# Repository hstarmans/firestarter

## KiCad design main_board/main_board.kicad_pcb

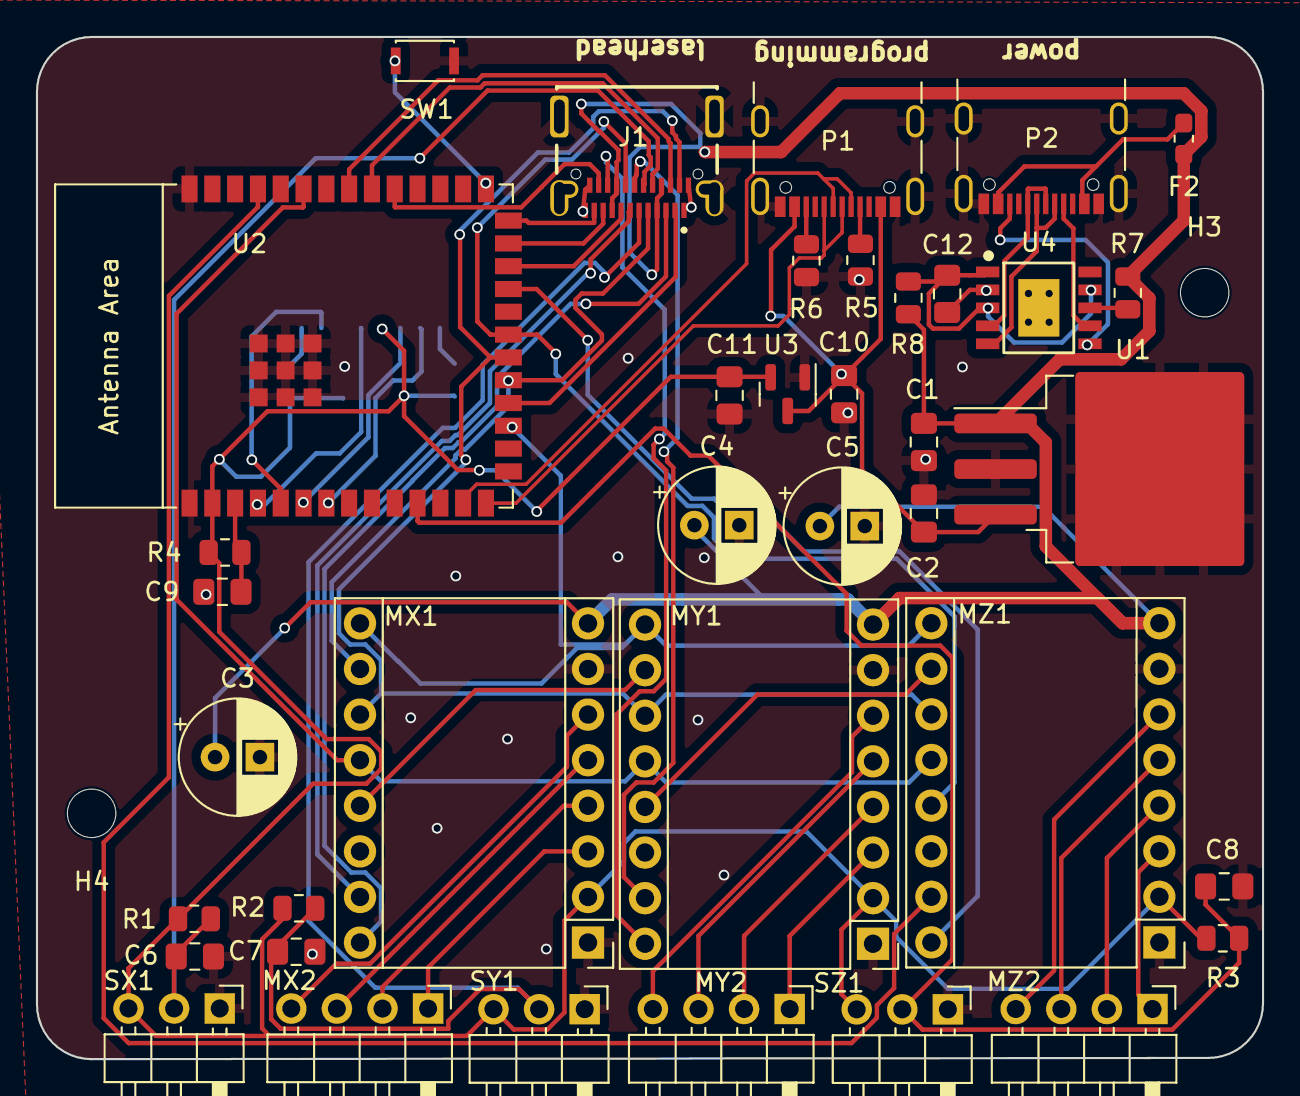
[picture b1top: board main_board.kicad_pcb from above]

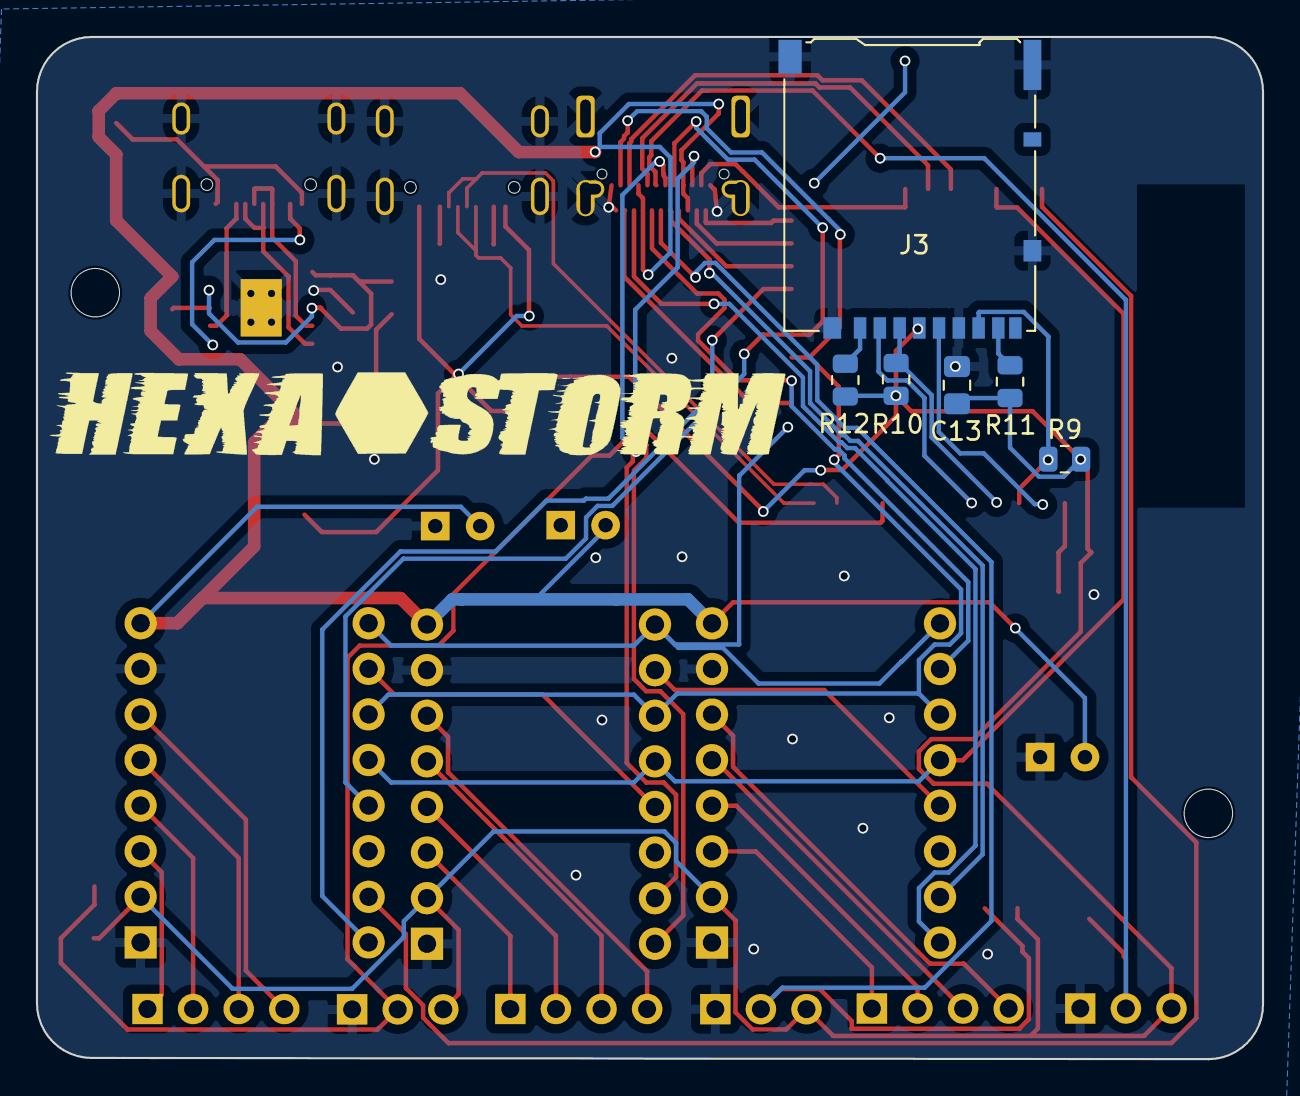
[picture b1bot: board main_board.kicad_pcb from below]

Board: 2 copper layers, 68.3 x 56.9 mm, 47 parts (7 on the bottom side), 58 nets.

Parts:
C1: 0.33mF; C_0805_2012Metric_Pad1.18x1.45mm_HandSolder
C2: 0.1mF; C_0805_2012Metric_Pad1.18x1.45mm_HandSolder
C3, C4, C5: 100uF; CP_Radial_D6.3mm_P2.50mm
C6, C7, C8: 0.1uF; C_0805_2012Metric_Pad1.18x1.45mm_HandSolder
C9, C12: 1uF; C_0805_2012Metric_Pad1.18x1.45mm_HandSolder
C10, C11: 1mF; C_0805_2012Metric_Pad1.18x1.45mm_HandSolder
C13: 0.1U; C_0805_2012Metric_Pad1.18x1.45mm_HandSolder
F2: Fuse; Fuse_0603_1608Metric_Pad1.05x0.95mm_HandSolder
G1: hexastorm
H3, H4: MountingHole; MountingHole_2.7mm_M2.5
J1: USB_C_Receptacle; GCT_USB4080-03-A_REVA1
J3: Micro_SD_Card_Det_Hirose_DM3AT; microSD_HC_Hirose_DM3AT-SF-PEJM5
MX1: X_STEPPER; TMC2130
MX2: MOLEX_2041; PinHeader_1x04_P2.54mm_Horizontal
MY1: Y_STEPPER; TMC2130
MY2: MOLEX_2041; PinHeader_1x04_P2.54mm_Horizontal
MZ1: Z_STEPPER; TMC2130
MZ2: MOLEX_2041; PinHeader_1x04_P2.54mm_Horizontal
P1, P2: USB_C_Plug_USB2.0; USB_C_Receptacle_GCT_USB4105-xx-A_16P_TopMnt_Horizontal
R1, R2, R3, R4, R7, R9, R10, R11, R12: 10K; R_0805_2012Metric
R5, R6: 5.1K; R_0805_2012Metric
R8: 1K; R_0805_2012Metric
SW1: SW_Push_Open; SW_SPST_CK_KXT3
SX1: MOLEX_2031; PinHeader_1x03_P2.54mm_Horizontal
SY1: MOLEX_2031; PinHeader_1x03_P2.54mm_Horizontal
SZ1: MOLEX_2031; PinHeader_1x03_P2.54mm_Horizontal
U1: LM7805_TO263; TO-263-3_TabPin2
U2: ESP32-S3-WROOM-2
U3: MCP1700x-330xxTT; SOT-23
U4: CH224K; ESSOP-10_CH224K

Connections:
+3.3V: C11.1, C13.1, J3.4 (VDD), MX1.10 (VDD), MY1.10 (VDD), MZ1.10 (VDD), R1.1, R2.1, R3.1, R4.1, R9.2, R10.1, R11.2, R12.1, SX1.3, SY1.3, SZ1.3, U2.2 (3V3), U3.2 (VO)
+5V: C2.1, C10.1, P1.A4 (VBUS), P1.A9 (VBUS), P1.B4 (VBUS), P1.B9 (VBUS), U1.3 (VO), U3.3 (VI)
+12V: C1.1, C3.2, C4.2, C5.2, F2.2, J1.A4 (VBUS), J1.A9 (VBUS), J1.B4 (VBUS), J1.B9 (VBUS), MX1.16 (VMOT), MY1.16 (VMOT), MZ1.16 (VMOT), R7.1, R8.2, U1.1 (VI)
CC1: P2.A5 (CC1), U4.7 (CC1)
CC2: P2.B5 (CC2), U4.6 (CC2)
CFG_DONE: J1.B2 (TX2+), U2.31 (GPIO38/FSPIWP/SUBSPIWP)
CFG_RST: J1.A8 (SBU1), U2.24 (GPIO47/SPICLK_P/SUBSPICLK_P_DIFF)
D+: P1.A6 (D+), P1.B6 (D+), U2.14 (GPIO20/U1CTS/ADC2_CH9/CLK_OUT1/USB_D+)
D-: P1.A7 (D-), P1.B7 (D-), U2.13 (GPIO19/U1RTS/ADC2_CH8/CLK_OUT2/USB_D-)
DM: P2.A7 (D-), P2.B7 (D-), U4.5 (DM)
DP: P2.A6 (D+), P2.B6 (D+), U4.4 (DP)
FREE: J1.B8 (SBU2), U2.32 (MTCK/GPIO39/CLK_OUT3/SUBSPICS1)
GND: C1.2, C2.2, C3.1, C4.1, C5.1, C6.1, C7.1, C8.1, C9.2, C10.2, C11.2, C12.2, C13.2, J1.A1 (GND), J1.A12 (GND), J1.B1 (GND), J1.B12 (GND), J1.S1 (SHIELD), J3.6 (VSS), J3.11 (SHIELD), MX1.9 (GND), MX1.15 (GND), MY1.9 (GND), MY1.15 (GND), MZ1.9 (GND), MZ1.15 (GND), P1.A1 (GND), P1.A12 (GND), P1.B1 (GND), P1.B12 (GND), P1.S1 (SHIELD), P2.A1 (GND), P2.A12 (GND), P2.B1 (GND), P2.B12 (GND), P2.S1 (SHIELD), R5.2, R6.2, SW1.2, SX1.1, SY1.1, SZ1.1, U1.2 (GND), U2.1 (GND), U2.40 (GND), U2.41 (GND), U3.1 (GND), U4.0 (GND), U4.2 (CFG2)
unnamed: J3.8 (DAT1), R11.1
unnamed: J3.1 (DAT2), R12.2
unnamed: P1.A5 (CC1), R5.1
unnamed: P1.B5 (CC2), R6.1
unnamed: C9.1, R4.2, U2.3 (EN)
unnamed: SW1.1, U2.27 (GPIO0/BOOT)
unnamed: R7.2, U4.8 (VBUS)
POT_SCL: J1.A2 (TX1+), U2.18 (GPIO10/TOUCH10/ADC1_CH9/FSPICS0/FSPIIO4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)
POT_SDA: J1.A10 (RX2-), U2.25 (GPIO48/SPICLK_N/SUBSPICLK_N_DIFF)
SD_CLK: J3.5 (CLK), U2.4 (GPIO4/TOUCH4/ADC1_CH3)
SD_MISO: J3.7 (DAT0), R9.1, U2.5 (GPIO5/TOUCH5/ADC1_CH4)
SD_MOSI: J3.3 (CMD), R10.2, U2.6 (GPIO6/TOUCH6/ADC1_CH5)
SD_SS: J3.2 (DAT3/CD), U2.7 (GPIO7/TOUCH7/ADC1_CH6)
SPI_SCK: J1.B11 (RX1+), MX1.3 (SCK), MY1.3 (SCK), MZ1.3 (SCK), U2.20 (GPIO12/TOUCH12/ADC2_CH1/FSPICLK/FSPIIO6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)
SPI_SI: J1.A5 (CC1), MX1.2 (SDI), U2.19 (GPIO11/TOUCH11/ADC2_CH0/FSPID/FSPIIO5/S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)
SPI_SO: J1.B5 (CC2), MZ1.5 (SDO), U2.21 (GPIO13/TOUCH13/ADC2_CH2/FSPIQ/FSPIIO7/S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)
SPI_SS_FLASH: J1.B10 (RX1-), U2.33 (MTDO/GPIO40/CLK_OUT2)
SPI_SS_FPGA: J1.A11 (RX2+), U2.26 (GPIO45)
SPI_SS_MOTOR: MX1.4 (CS), MY1.4 (CS), MZ1.4 (CS), U2.35 (MTMS/GPIO42)
SPI_XOYI: MX1.5 (SDO), MY1.2 (SDI)
SPI_YOZI: MY1.5 (SDO), MZ1.2 (SDI)
STEP_ENABLE: MX1.1 (~EN), MY1.1 (~EN), MZ1.1 (~EN), U2.17 (GPIO9/TOUCH9/ADC1_CH8/FSPIHD/SUBSPIHD)
VBUS: F2.1, P2.A4 (VBUS), P2.A9 (VBUS), P2.B4 (VBUS), P2.B9 (VBUS)
VDD: C12.1, R8.1, U4.1 (VDD), U4.3 (CFG3), U4.9 (CFG1)
X_1A: MX1.12 (M1A), MX2.2
X_1B: MX1.11 (M1B), MX2.1
X_2A: MX1.13 (M2A), MX2.3
X_2B: MX1.14 (M2B), MX2.4
X_DIR: J1.A3 (TX1-), MX1.8 (DIR)
X_PO: C6.2, J1.B7 (D-), R1.2, SX1.2
X_STEP: J1.A7 (D-), MX1.7 (STEP)
Y_1A: MY1.12 (M1A), MY2.2
Y_1B: MY1.11 (M1B), MY2.1
Y_2A: MY1.13 (M2A), MY2.3
Y_2B: MY1.14 (M2B), MY2.4
Y_DIR: J1.B3 (TX2-), MY1.8 (DIR)
Y_PO: C7.2, J1.A6 (D+), R2.2, SY1.2
Y_STEP: J1.B6 (D+), MY1.7 (STEP)
Z_1A: MZ1.12 (M1A), MZ2.2
Z_1B: MZ1.11 (M1B), MZ2.1
Z_2A: MZ1.13 (M2A), MZ2.3
Z_2B: MZ1.14 (M2B), MZ2.4
Z_DIR: MZ1.8 (DIR), U2.23 (GPIO21)
Z_PO: C8.2, R3.2, SZ1.2, U2.11 (GPIO18/U1RXD/ADC2_CH7/CLK_OUT3)
Z_STEP: MZ1.7 (STEP), U2.37 (U0TXD/GPIO43/CLK_OUT1)

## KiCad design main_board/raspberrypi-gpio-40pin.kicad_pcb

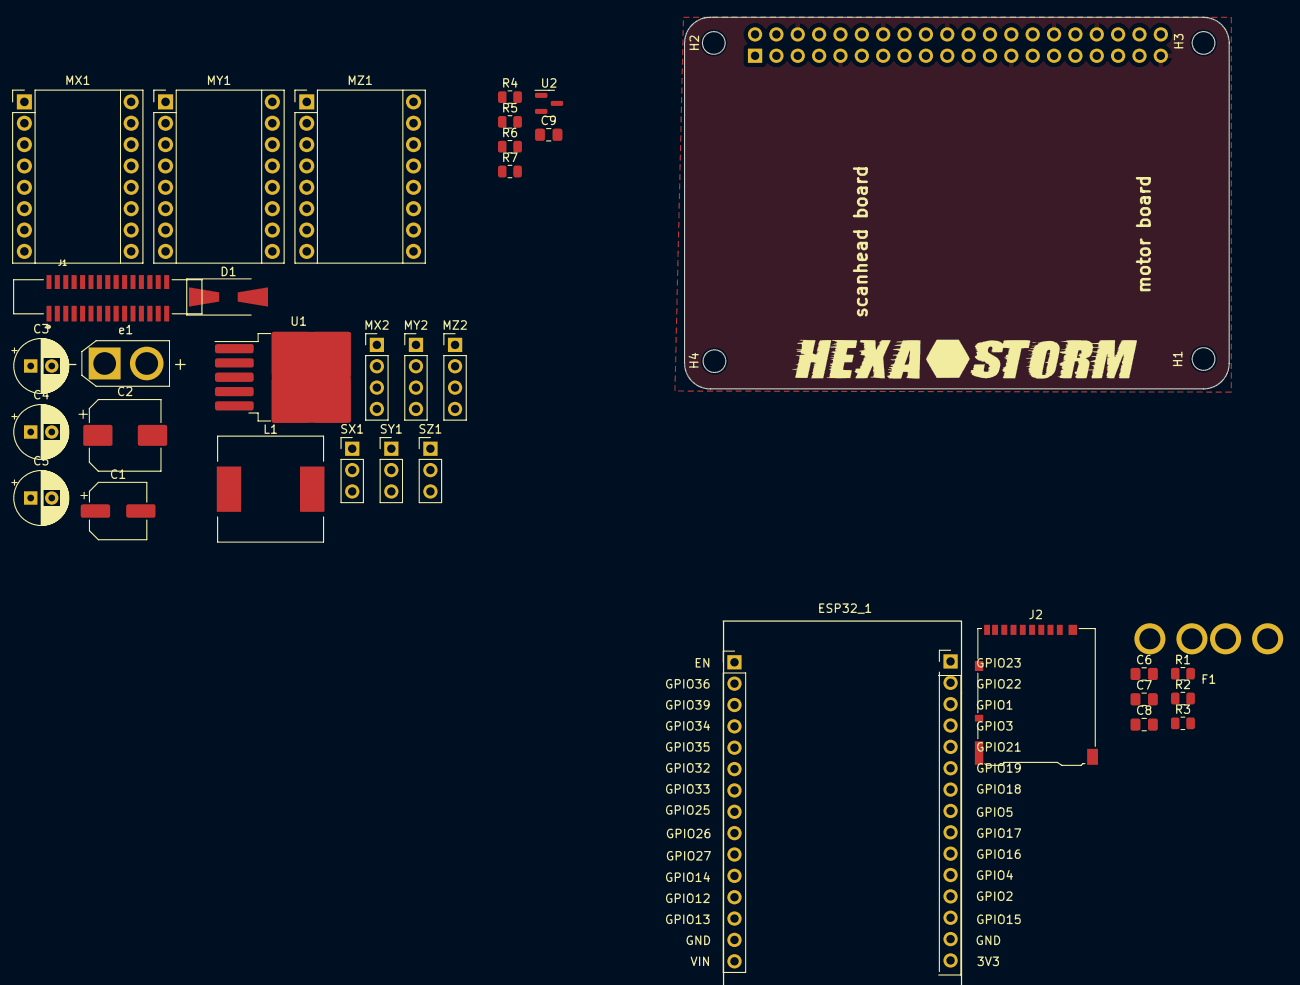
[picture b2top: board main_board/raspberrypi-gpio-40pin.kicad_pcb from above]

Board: 2 copper layers, 64.8 x 44.2 mm, 40 parts (1 on the bottom side), 48 nets, no tracks yet.

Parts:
C1: 330 uF; CP_Elec_6.3x7.7
C2: 220 uF; CP_Elec_8x10
C3, C4, C5: 100uF; CP_Radial_D6.3mm_P2.50mm
C6, C7, C8: 0.1uF; C_0805_2012Metric_Pad1.18x1.45mm_HandSolder
C9: 0.1U; C_0805_2012Metric_Pad1.18x1.45mm_HandSolder
D1: SS320-HF; D_SMA-SMB_Universal_Handsoldering
ESP32_1: ESP32_Devkit_DOIT_V1
F1: 30A; MCCQ-121
G1: hexastorm
H1, H2, H3, H4: MountingHole; MountingHole_2.7mm_M2.5
J1: 1-1734248-5; TE_1-1734248-5
J2: Micro_SD_Card_Det_Hirose_DM3AT; microSD_HC_Hirose_DM3AT-SF-PEJM5
L1: 33 uH; L_12x12mm_H6mm
MX1: X_STEPPER; TMC2130
MX2: MOLEX_2041; PinHeader_1x04_P2.54mm_Vertical
MY1: Y_STEPPER; TMC2130
MY2: MOLEX_2041; PinHeader_1x04_P2.54mm_Vertical
MZ1: Z_STEPPER; TMC2130
MZ2: MOLEX_2041; PinHeader_1x04_P2.54mm_Vertical
P1: Conn_02x20_Odd_Even; PinSocket_2x20_P2.54mm_Vertical
R1, R2, R3, R4, R5, R6, R7: 10K; R_0805_2012Metric
SX1: MOLEX_2031; PinHeader_1x03_P2.54mm_Vertical
SY1: MOLEX_2031; PinHeader_1x03_P2.54mm_Vertical
SZ1: MOLEX_2031; PinHeader_1x03_P2.54mm_Vertical
U1: LM2596S-5; TO-263-5_TabPin3
U2: MCP1700x-330xxTT; SOT-23
e1: Screw_Terminal_01x02; AMASS_XT30U-F_1x02_P5.0mm_Vertical

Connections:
+3.3V: C9.1, ESP32_1.16 (3V3), J2.4 (VDD), MX1.10 (VDD), MY1.10 (VDD), MZ1.10 (VDD), P1.1, P1.17, R1.1, R2.1, R3.1, R4.2, R5.1, R6.1, R7.2, SX1.1, SY1.1, SZ1.1, U2.2 (VO)
+5V: C2.1, ESP32_1.15 (VIN), L1.2, P1.2, P1.4, U1.4 (FB), U2.3 (VI)
+12V: C1.1, C3.2, C4.2, C5.2, F1.3, F1.4, MX1.16 (VMOT), MY1.16 (VMOT), MZ1.16 (VMOT), U1.1 (VIN)
CFG_DONE: ESP32_1.7 (GPIO33), J1.6, J1.6_1 (6), P1.29
CFG_RST: ESP32_1.28 (GPIO1), J1.7, J1.7_1 (7), P1.37
ENABLE: ESP32_1.27 (GPIO3), MX1.1 (~EN), MY1.1 (~EN), MZ1.1 (~EN), P1.11
GND: C1.2, C2.2, C3.1, C4.1, C5.1, C6.1, C7.1, C8.1, C9.2, D1.2 (A), ESP32_1.14 (GND), ESP32_1.17 (GND), J1.1, J1.1_1 (1), J2.6 (VSS), J2.11 (SHIELD), MX1.9 (GND), MX1.15 (GND), MY1.9 (GND), MY1.15 (GND), MZ1.9 (GND), MZ1.15 (GND), P1.6, P1.9, P1.14, P1.20, P1.25, P1.30, P1.34, P1.39, SX1.3, SY1.3, SZ1.3, U1.3 (GND), U1.5 (~ON/OFF), U2.1 (GND), e1.1
unnamed: D1.1 (K), L1.1, U1.2 (OUT)
unnamed: J2.8 (DAT1), R7.1
unnamed: J2.1 (DAT2), R6.2
unnamed: F1.1, F1.2, e1.2
POT_SCL: ESP32_1.29 (GPIO22), J1.2, J1.2_1 (2), P1.5
POT_SDA: ESP32_1.26 (GPIO21), J1.3, J1.3_1 (3), P1.3
SD_CLK: ESP32_1.24 (GPIO18), J2.5 (CLK)
SD_IO2: ESP32_1.4 (GPIO34), J1.13, J1.13_1 (13), P1.18
SD_IO3: ESP32_1.5 (GPIO35), J1.15, J1.15_1 (15), P1.22
SD_MISO: ESP32_1.25 (GPIO19), J2.7 (DAT0), R4.1
SD_MOSI: ESP32_1.30 (GPIO23), J2.3 (CMD), R5.2
SD_SS: ESP32_1.23 (GPIO5), J2.2 (DAT3/CD)
SPI_SCK: ESP32_1.6 (GPIO32), J1.14, J1.14_1 (14), MX1.3 (SCK), MY1.3 (SCK), MZ1.3 (SCK), P1.40
SPI_SI: ESP32_1.9 (GPIO26), J1.9, J1.9_1 (9), MX1.2 (SDI), P1.38
SPI_SO: ESP32_1.8 (GPIO25), J1.12, J1.12_1 (12), MZ1.5 (SDO), P1.35
SPI_SS: ESP32_1.10 (GPIO27), J1.10, J1.10_1 (10), MZ1.4 (CS), P1.24
SPI_SS2: J1.11, J1.11_1 (11), P1.36
SPI_SS3: ESP32_1.22 (GPIO17), MX1.4 (CS), MY1.4 (CS), P1.26
SPI_XOYI: MX1.5 (SDO), MY1.2 (SDI)
SPI_YOZI: MY1.5 (SDO), MZ1.2 (SDI)
X_1A: MX1.12 (M1A), MX2.3
X_1B: MX1.11 (M1B), MX2.4
X_2A: MX1.13 (M2A), MX2.2
X_2B: MX1.14 (M2B), MX2.1
X_DIR: J1.4, J1.4_1 (4), MX1.8 (DIR)
X_PO: C6.2, J1.8, J1.8_1 (8), R1.2, SX1.2
X_STEP: J1.5, J1.5_1 (5), MX1.7 (STEP)
Y_1A: MY1.12 (M1A), MY2.3
Y_1B: MY1.11 (M1B), MY2.4
Y_2A: MY1.13 (M2A), MY2.2
Y_2B: MY1.14 (M2B), MY2.1
Y_DIR: ESP32_1.13 (GPIO13), MY1.8 (DIR), P1.10
Y_PO: C7.2, ESP32_1.21 (GPIO16), P1.12, R2.2, SY1.2
Y_STEP: ESP32_1.12 (GPIO12), MY1.7 (STEP), P1.8
Z_1A: MZ1.12 (M1A), MZ2.3
Z_1B: MZ1.11 (M1B), MZ2.4
Z_2A: MZ1.13 (M2A), MZ2.2
Z_2B: MZ1.14 (M2B), MZ2.1
Z_DIR: ESP32_1.3 (GPIO39), MZ1.8 (DIR), P1.21
Z_PO: C8.2, ESP32_1.11 (GPIO14), P1.23, R3.2, SZ1.2
Z_STEP: ESP32_1.2 (GPIO36), MZ1.7 (STEP), P1.19

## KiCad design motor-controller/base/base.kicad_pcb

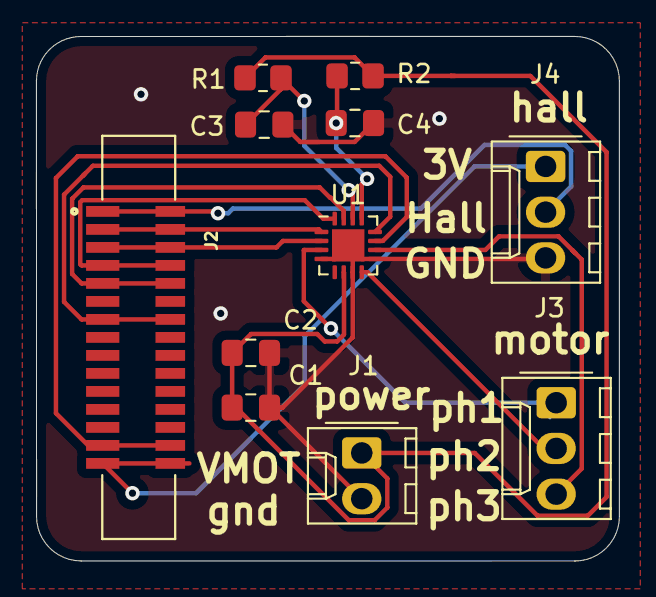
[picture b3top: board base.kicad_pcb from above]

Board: 2 copper layers, 32.4 x 29.1 mm, 11 parts (0 on the bottom side), 15 nets.

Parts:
C1, C3, C4: 10nF; C_0805_2012Metric_Pad1.18x1.45mm_HandSolder
C2: 100nF; C_0805_2012Metric_Pad1.18x1.45mm_HandSolder
J1: Conn_01x02; Molex_KK-254_AE-6410-02A_1x02_P2.54mm_Vertical
J2: 1-1734248-5; TE_1-1734248-5
J3, J4: Conn_01x03; Molex_KK-254_AE-6410-03A_1x03_P2.54mm_Vertical
R1, R2: 10K; R_0805_2012Metric_Pad1.20x1.40mm_HandSolder
U1: STSPIN230; VQFN-16-1EP_3x3mm_P0.5mm_EP1.8x1.8mm

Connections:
+3V3: J2.15, J2.15_1, J4.1
+5V: C1.1, C2.1, J1.1, R1.1, R2.1, U1.6
GND: C1.2, C2.2, C3.2, C4.2, J1.2, J4.3, U1.4, U1.7, U1.9, U1.17
HALL: J2.1, J2.1_1, J4.2
unnamed: C3.1, R1.2, U1.14
unnamed: C4.1, R2.2, U1.13
PH1: J3.1, U1.3
PH2: J3.2, U1.8
PH3: J3.3, U1.10
PWM1H: J2.2, J2.2_1, U1.1
PWM1L: J2.3, J2.3_1, U1.2
PWM2H: J2.4, J2.4_1, U1.16
PWM2L: J2.5, J2.5_1, U1.15
PWM3H: J2.7, J2.7_1, U1.12
PWM3L: J2.14, J2.14_1, U1.11

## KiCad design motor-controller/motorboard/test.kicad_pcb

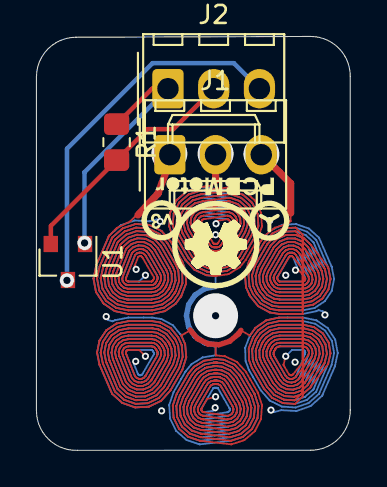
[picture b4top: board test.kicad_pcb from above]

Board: 4 copper layers, 17.4 x 23.0 mm, 4 parts (0 on the bottom side), 4 nets.

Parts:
J1, J2: Conn_01x03; Molex_KK-254_AE-6410-03A_1x03_P2.54mm_Vertical
R1: 10K; R_0805_2012Metric_Pad1.20x1.40mm_HandSolder
U1: DRV5015A3QDBZR; SOT-23

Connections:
+3V3: J2.1, R1.1, U1.1
GND: J2.3, U1.3
HALL: J2.2, R1.2, U1.2
PH1: J1.1, J1.2, J1.3

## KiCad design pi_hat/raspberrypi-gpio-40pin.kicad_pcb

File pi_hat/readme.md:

# Firestarter
This is a hat for a Raspberry pi. It enables one to control a prism scanner and cut boards with a spindle using a FPGA.
Similar boards are; beaglewire, icezero, [blackice2](https://github.com/mystorm-org/BlackIce-II)
and the [Icecore](https://github.com/folknology/IceCore)

The hat has the following features;
 - PWM control of spindle and fan
 - Control 3 stepper motors with TMC2130 driver
 - Three limit switches
 - voltage converters from 3V to 1.1V to supply FPGA with power
 - Ice40HX4K FPGA
 - Flash memory to store bitstream for FPGA
 - simple board; only two layers and no BGA components
 
# Status
The board has been tested. A user can upload data to the FPGA, rotate polygon, enable the laser and store data on the SRAM.
The motor drivers and spindle have not been tested but should be working.
 
# Possible improvements
- SDIO connector not connected to FPGA. This is faster than SPI.
- Ground of the stepper capacitor is denoted on board as 12 V
- chip select SPI 1 is connected to GPIO7, this should be GPIO 18.

# Schema

# Image
Not yet build.

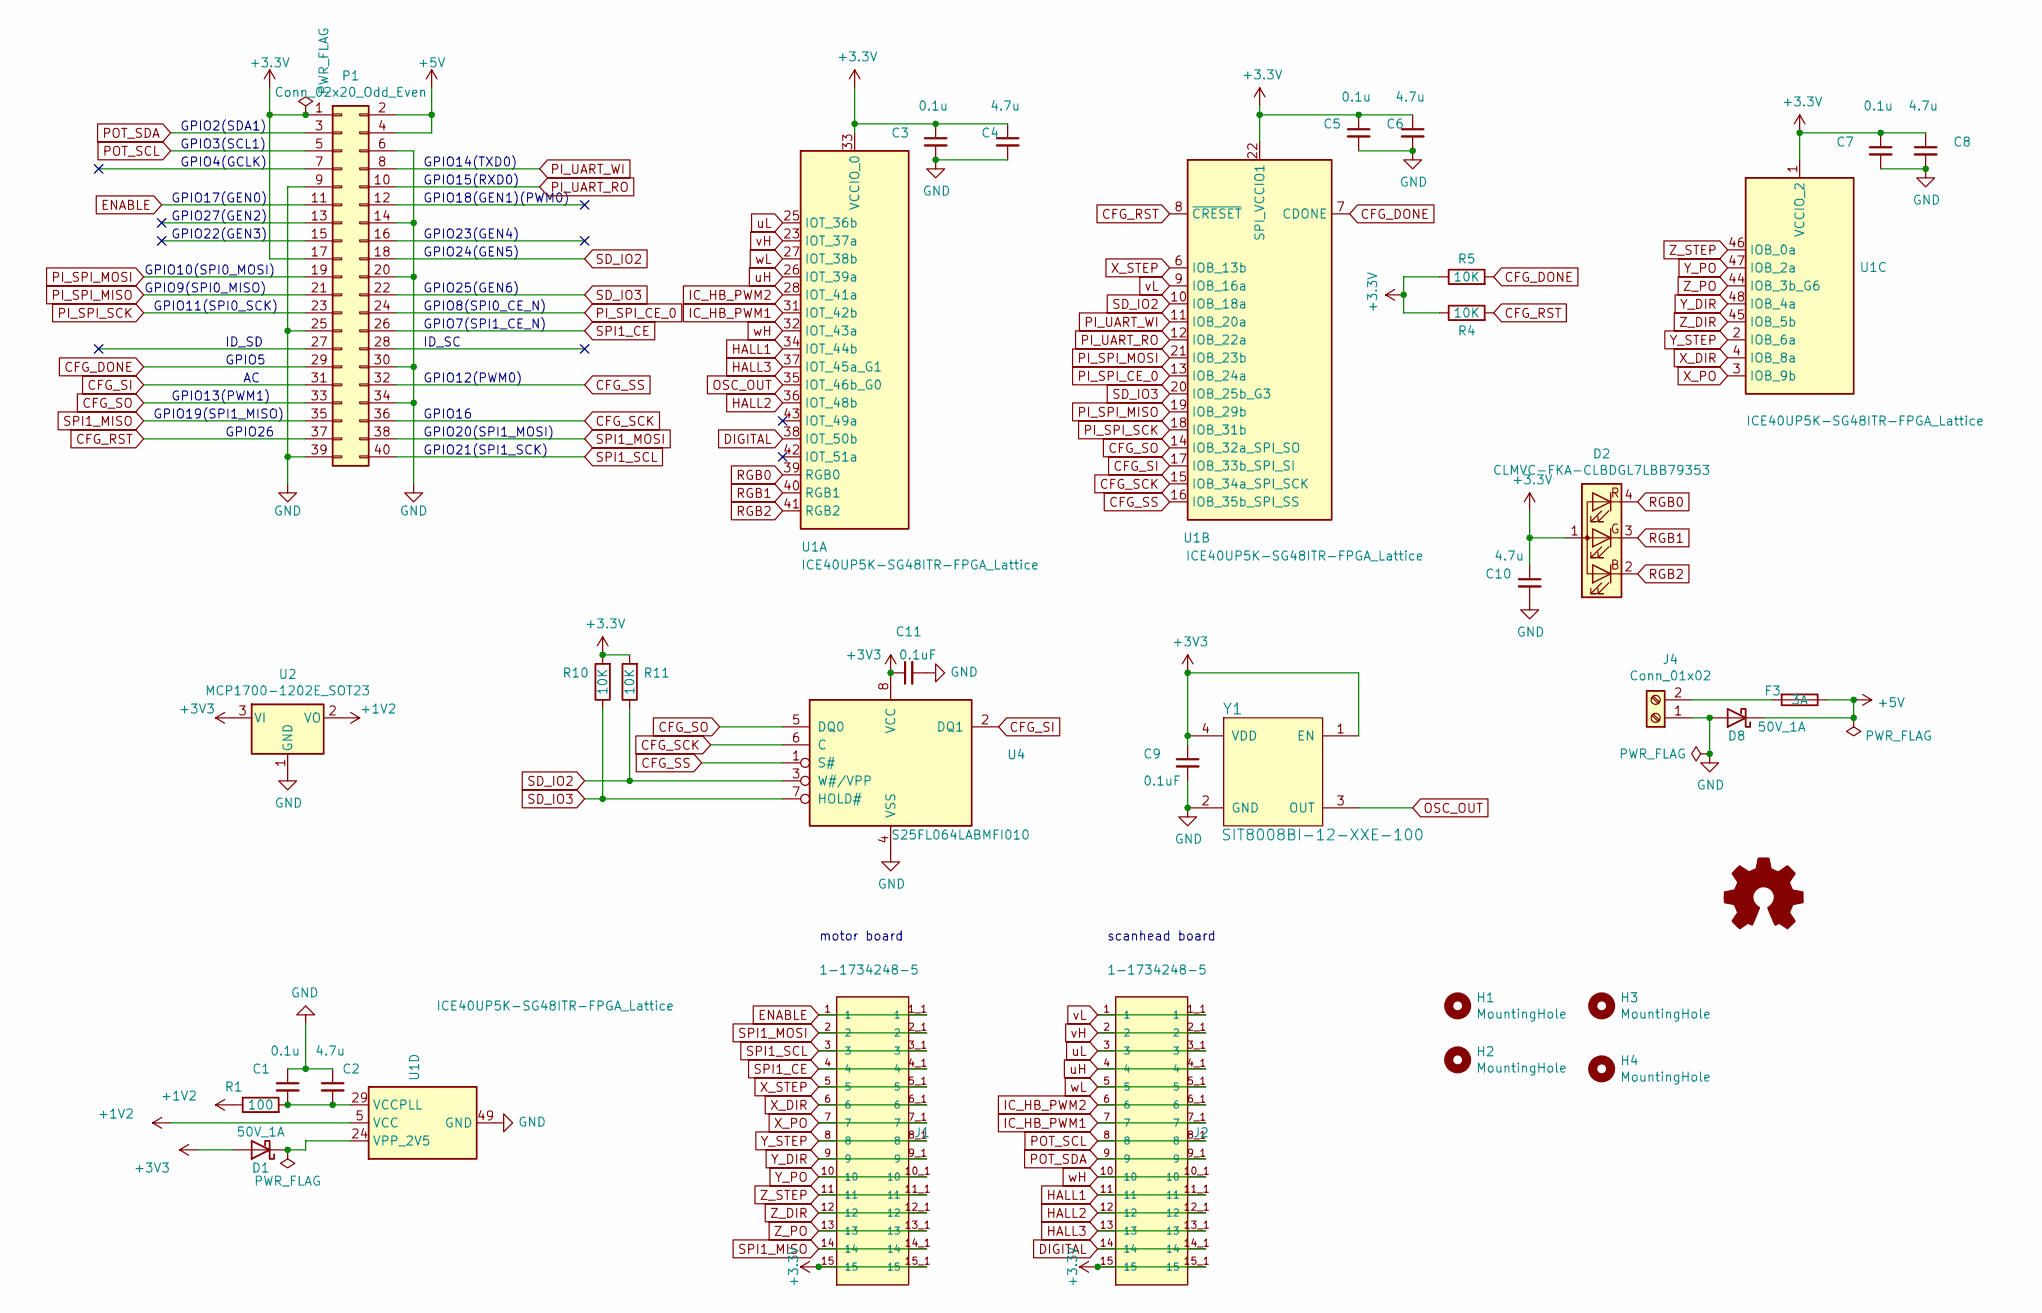
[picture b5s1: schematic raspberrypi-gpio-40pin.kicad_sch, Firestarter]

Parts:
C1, C3, C5, C7: 0.1u; C_0805_2012Metric_Pad1.18x1.45mm_HandSolder
C2, C4, C6, C8: 4.7u; C_0805_2012Metric_Pad1.18x1.45mm_HandSolder
C9: 0.1uF; C_0805_2012Metric_Pad1.15x1.40mm_HandSolder
C10: 4.7u; C_0805_2012Metric_Pad1.15x1.40mm_HandSolder
C11: 0.1uF; C_0805_2012Metric_Pad1.18x1.45mm_HandSolder
D1, D8: 50V_1A; D_SMA_Handsoldering
D2: CLMVC-FKA-CLBDGL7LBB79353; LED_Cree-PLCC4_2x2mm_CW
F3: 3A; Fuse_1206_3216Metric
G1: hexastorm
H1, H2, H3, H4: MountingHole; MountingHole_2.7mm_M2.5
J1, J2: 1-1734248-5; TE_1-1734248-5; PARTREV E1
J4: Conn_01x02; TerminalBlock_Phoenix_MKDS-1,5-2-5.08_1x02_P5.08mm_Horizont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
P1: Conn_02x20_Odd_Even; PinSocket_2x20_P2.54mm_Vertical
R1: 100; R_0805_2012Metric_Pad1.15x1.40mm_HandSolder
R4, R5, R10, R11: 10K; R_0805_2012Metric_Pad1.15x1.40mm_HandSolder
U1: ICE40UP5K-SG48ITR-FPGA_Lattice; QFN-48-1EP_7x7mm_P0.5mm_EP5.6x5.6mm
U2: MCP1700-1202E_SOT23; SOT-23
U4: S25FL064LABMFI010; SOIJ-8_5.3x5.3mm_P1.27mm
Y1: SIT8008BI-12-XXE-100; ASDMB-100.000MHZ-XY-T

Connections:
+1V2: R1.1, U1.5 (VCC), U1.30 (VCC), U2.2 (VO)
+5V: D8.1 (K), F3.1, P1.2, P1.4
CFG_DONE: P1.29, R5.2, U1.7 (CDONE)
CFG_RST: P1.37, R4.2, U1.8 (~CRESET)
CFG_SCK: P1.36, U1.15 (IOB_34a_SPI_SCK), U4.6 (C)
CFG_SI: P1.31, U1.17 (IOB_33b_SPI_SI), U4.2 (DQ1)
CFG_SO: P1.33, U1.14 (IOB_32a_SPI_SO), U4.5 (DQ0)
CFG_SS: P1.32, U1.16 (IOB_35b_SPI_SS), U4.1 (S#)
DIGITAL: J2.14, J2.14_1 (14), U1.38 (IOT_50b)
ENABLE: J1.1, J1.1_1 (1), P1.11
GND: C1.1, C2.1, C3.2, C4.2, C5.2, C6.2, C7.2, C8.2, C9.2, C10.2, C11.2, D8.2 (A), J4.1, P1.6, P1.9, P1.14, P1.20, P1.25, P1.30, P1.34, P1.39, U1.49 (GND), U2.1 (GND), U4.4 (VSS), Y1.2 (GND)
HALL1: J2.11, J2.11_1 (11), U1.34 (IOT_44b)
HALL2: J2.12, J2.12_1 (12), U1.36 (IOT_48b)
HALL3: J2.13, J2.13_1 (13), U1.37 (IOT_45a_G1)
IC_HB_PWM1: J2.7, J2.7_1 (7), U1.31 (IOT_42b)
IC_HB_PWM2: J2.6, J2.6_1 (6), U1.28 (IOT_41a)
unnamed: C1.2, C2.2, R1.2, U1.29 (VCCPLL)
unnamed: D1.1 (K), U1.24 (VPP_2V5)
unnamed: F3.2, J4.2
OSC_OUT: U1.35 (IOT_46b_G0), Y1.3 (OUT)
PI_SPI_CE_0: P1.24, U1.13 (IOB_24a)
PI_SPI_MISO: P1.21, U1.19 (IOB_29b)
PI_SPI_MOSI: P1.19, U1.21 (IOB_23b)
PI_SPI_SCK: P1.23, U1.18 (IOB_31b)
PI_UART_RO: P1.10, U1.12 (IOB_22a)
PI_UART_WI: P1.8, U1.11 (IOB_20a)
POT_SCL: J2.8, J2.8_1 (8), P1.5
POT_SDA: J2.9, J2.9_1 (9), P1.3
PWM1H: J2.4, J2.4_1 (4), U1.26 (IOT_39a)
PWM1L: J2.3, J2.3_1 (3), U1.25 (IOT_36b)
PWM2H: J2.2, J2.2_1 (2), U1.23 (IOT_37a)
PWM2L: J2.1, J2.1_1 (1), U1.9 (IOB_16a)
PWM3H: J2.10, J2.10_1 (10), U1.32 (IOT_43a)
PWM3L: J2.5, J2.5_1 (5), U1.27 (IOT_38b)
RGB0: D2.4 (BK), U1.39 (RGB0)
RGB1: D2.3 (GK), U1.40 (RGB1)
RGB2: D2.2 (RK), U1.41 (RGB2)
SD_IO2: P1.18, R11.1, U1.10 (IOB_18a), U4.3 (W#/VPP)
SD_IO3: P1.22, R10.1, U1.20 (IOB_25b_G3), U4.7 (HOLD#)
SPI1_CE: J1.4, J1.4_1 (4), P1.26
SPI1_MISO: J1.14, J1.14_1 (14), P1.35
SPI1_MOSI: J1.2, J1.2_1 (2), P1.38
SPI1_SCL: J1.3, J1.3_1 (3), P1.40
X_DIR: J1.6, J1.6_1 (6), U1.4 (IOB_8a)
X_PO: J1.7, J1.7_1 (7), U1.3 (IOB_9b)
X_STEP: J1.5, J1.5_1 (5), U1.6 (IOB_13b)
Y_DIR: J1.9, J1.9_1 (9), U1.48 (IOB_4a)
Y_PO: J1.10, J1.10_1 (10), U1.47 (IOB_2a)
Y_STEP: J1.8, J1.8_1 (8), U1.2 (IOB_6a)
Z_DIR: J1.12, J1.12_1 (12), U1.45 (IOB_5b)
Z_PO: J1.13, J1.13_1 (13), U1.44 (IOB_3b_G6)
Z_STEP: J1.11, J1.11_1 (11), U1.46 (IOB_0a)

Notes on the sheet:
GPIO21(SPI1_SCK)
GPIO4(GCLK)
GPIO11(SPI0_SCK)
GPIO18(GEN1)(PWM0)
GPIO15(RXD0)
GPIO19(SPI1_MISO)
GPIO25(GEN6)
GPIO14(TXD0)
GPIO5
GPIO12(PWM0)
GPIO3(SCL1)
GPIO22(GEN3)
GPIO26
GPIO16
GPIO27(GEN2)
GPIO8(SPI0_CE_N)
GPIO2(SDA1)
ID_SD
GPIO20(SPI1_MOSI)
motor board
GPIO17(GEN0)
GPIO9(SPI0_MISO)
GPIO24(GEN5)
GPIO7(SPI1_CE_N)
GPIO10(SPI0_MOSI)
ID_SC
scanhead board
GPIO13(PWM1)
GPIO23(GEN4)

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
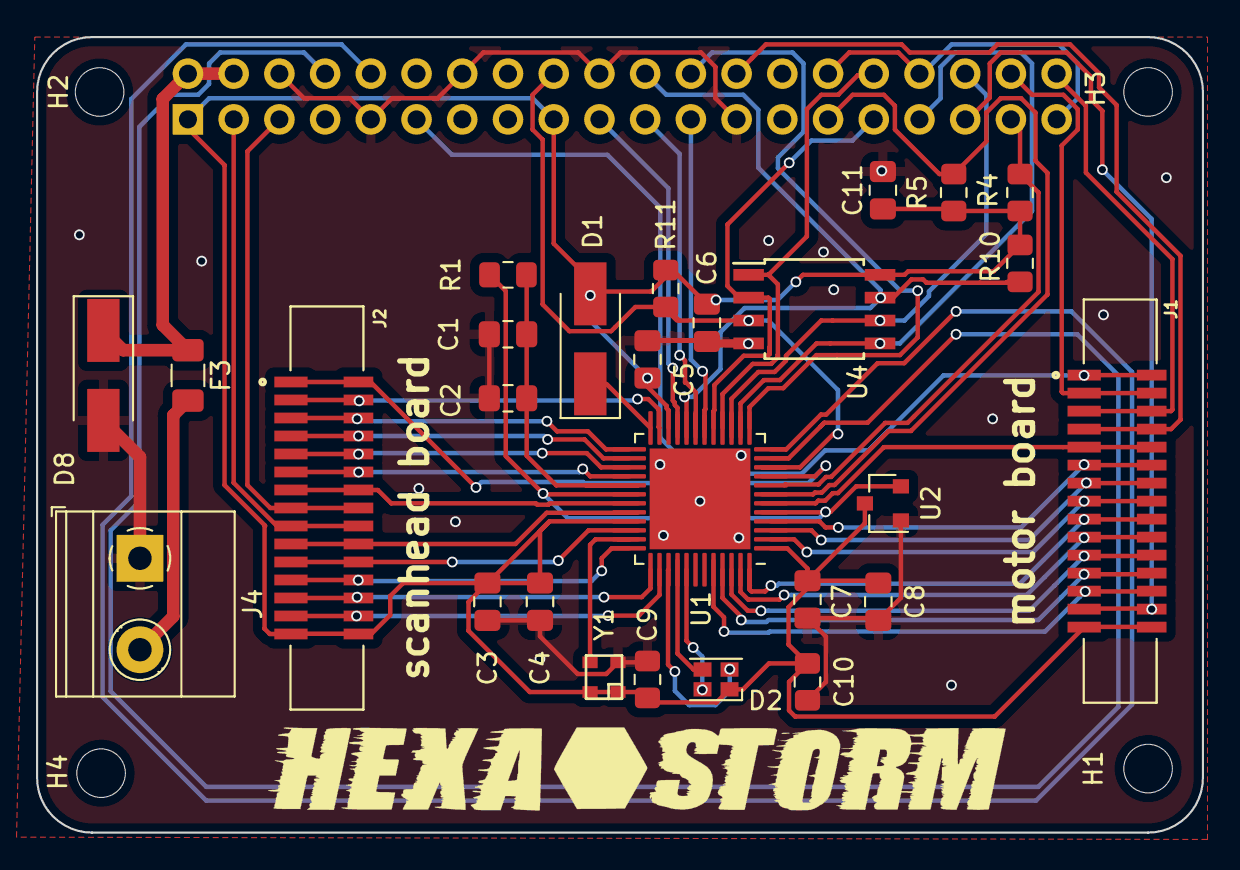
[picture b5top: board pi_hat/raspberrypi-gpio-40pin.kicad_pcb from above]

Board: 2 copper layers, 64.8 x 44.2 mm, 33 parts (1 on the bottom side), 53 nets.
